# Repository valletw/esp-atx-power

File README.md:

# ESP32 ATX Power Controller

The purpose of this project is to control a computer remotely by connecting
directly to the ATX motherboard power IO control. The control will be done with
Home Assistant by using [ESPHome](https://esphome.io) firmware.

Custom software could be written by using ESP-IDF SDK but it is not the purpose
of this project.

## Hardware

Double 2.54mm pin headers are set for each ATX functionalities to manage:

- `PWR SW`: ATX power button
- `RST SW`: ATX reset button
- `PWR LED`: ATX power state LED
- `HDD LED`: ATX HDD activity LED

Two status LED are available:

- `PWR`: 3.3V state
- `STAT`: System status controlled by software

Two buttons are available for ESP32 boot sequence:

- `BOOT`: Control processor download mode on boot
- `EN`: Control processor reset

For advanced debug, the following connectors are available:

- 2x5 1.27mm pins header JTAG/SWD for external probe
- 4-pins Molex connector for UART

### Components choice

This project is based on an ESP32-C3 module to simplify design and ensure good
WiFi performance (with external antenna connector). ESP32 has been selected for
the big community to generate software and the frameworks available. Espressif
hardware design rules has been take into account following there
[documentation](https://docs.espressif.com/projects/esp-hardware-design-guidelines/en/latest/esp32c3/pcb-layout-design.html)

For easy debug and flashing, ESP32 with USB-CDC and JTAG support has been selected.
It allows to remove the USB-UART bridge of the previous design.

The optocouplers for electric isolation have been selected following the
[PiKVM](https://github.com/pikvm/pikvm) project experience. In the
[DIY PiKVM V2 instructions](https://docs.pikvm.org/v2/), the OMRON reference is
recommended. Others relays/optocouplers may not be sensitive enough or low-level
controlled.

The 3.3V to power all the components is generated from an LDO using the 5V of the
USB socket. It can also be powered from external 5V on pins header. Both external
5V and USB can be connected at the same time, a power MUX is used to switch between
both sources.

All others components has been selected from [JLCPCB](https://jlcpcb.com/parts/)
catalogue to minimize the cost and the assembly fees.

### Manufacturing

The board is manufactured by [JLCPCB](https://jlcpcb.com), here is the details
you will require to generate an order.

*Note: JLCPCB requests some modifications on output files, do not use direct
export from KiCad (check the FAQ)*

#### PCB

Files: [Gerbers](jlcpcb/gerbers.zip)

Configuration              | Value
---------------------------|---------------------------------
Base Materiel              | FR-4
Layers                     | 4
Dimensions                 | 76.56 x 25.10
Different design           | 1
Delivery format            | Single PCB
PCB thickness              | 1.6
PCB color                  | Green (other colors have fees)
Silkscreen                 | White
Materiel type              | FR4-Standard TG 135-140
Surface finish             | HASL
Specify layer sequence     | F_Cu / In1_Cu / In2_Cu / B_Cu
Impedance control          | Yes
Layer stackup              | JLC04161H-7628
Via covering               | Tented
Min via hole size/diameter | 0.3mm/0.45mm
Remove order number        | Specify a location

*Note: All options have not been detail here, keep default value.*

#### Assembly

Files: [BOM](jlcpcb/bom.csv), [CPL](jlcpcb/cpl.csv)

Configuration       | Value
--------------------|--------------------
PCBA type           | Economic
Assembly side       | Top
Tooling holes       | Added by JLCPCB

Verify "pick & place" orientations and positions on the web viewer

JLCPCB will add 2 tooling holes for assembly (1 mm diameter near the board corners).

*Note: All options have not been detail here, keep default value.*

### ESP32 Pinout

For those who want to reuse this project, here is the ESP32 pinout to manage the
different input/output.

Name              | Pin  | Direction
------------------|------|----------
System Status LED | IO8  | Output (strapping pin)
ATX Power Button  | IO0  | Output
ATX Reset Button  | IO1  | Output
ATX Power State   | IO3  | Input
ATX HDD Activity  | IO10 | Input

## ESPHome configuration

Device must be setup via USB connection the first time to flash the customized
firmware with sensors/buttons configuration.

Once it has been configured successfully, you should fix the device IP on your
router for easier Home Assistant configuration.

Note: Installation can be bypassed if already done or you can use docker image.
Check [ESPHome documentation](https://esphome.io/guides/getting_started_command_line.html)
for more details.

### Installation

```shell
pip install esphome
# Ensure your user session has the correct permission for serial port.
sudo usermod -a -G dialout <USERNAME>
```

### Customize

Depending of your installation and network, a `secrets.yaml` file must be
create with your specific configuration.

```yaml
# secrets.yaml
hostname: MyControllerHostname
wifi_ssid: MySSID
wifi_password: MyStrongPassphrase
wifi_fb_ssid: ATX Controller Fallback Hotspot
wifi_fb_password: StrongPassphrase
ota_password: MyOTAPassphrase
api_key: 32BytesBase64String
```

### Compile and flash

```shell
# Generate the firmware.
esphome compile esphome.yaml
# Flash the firmware to the ESP.
esphome run esphome.yaml
# Get logs.
esphome logs esphome.yaml
```

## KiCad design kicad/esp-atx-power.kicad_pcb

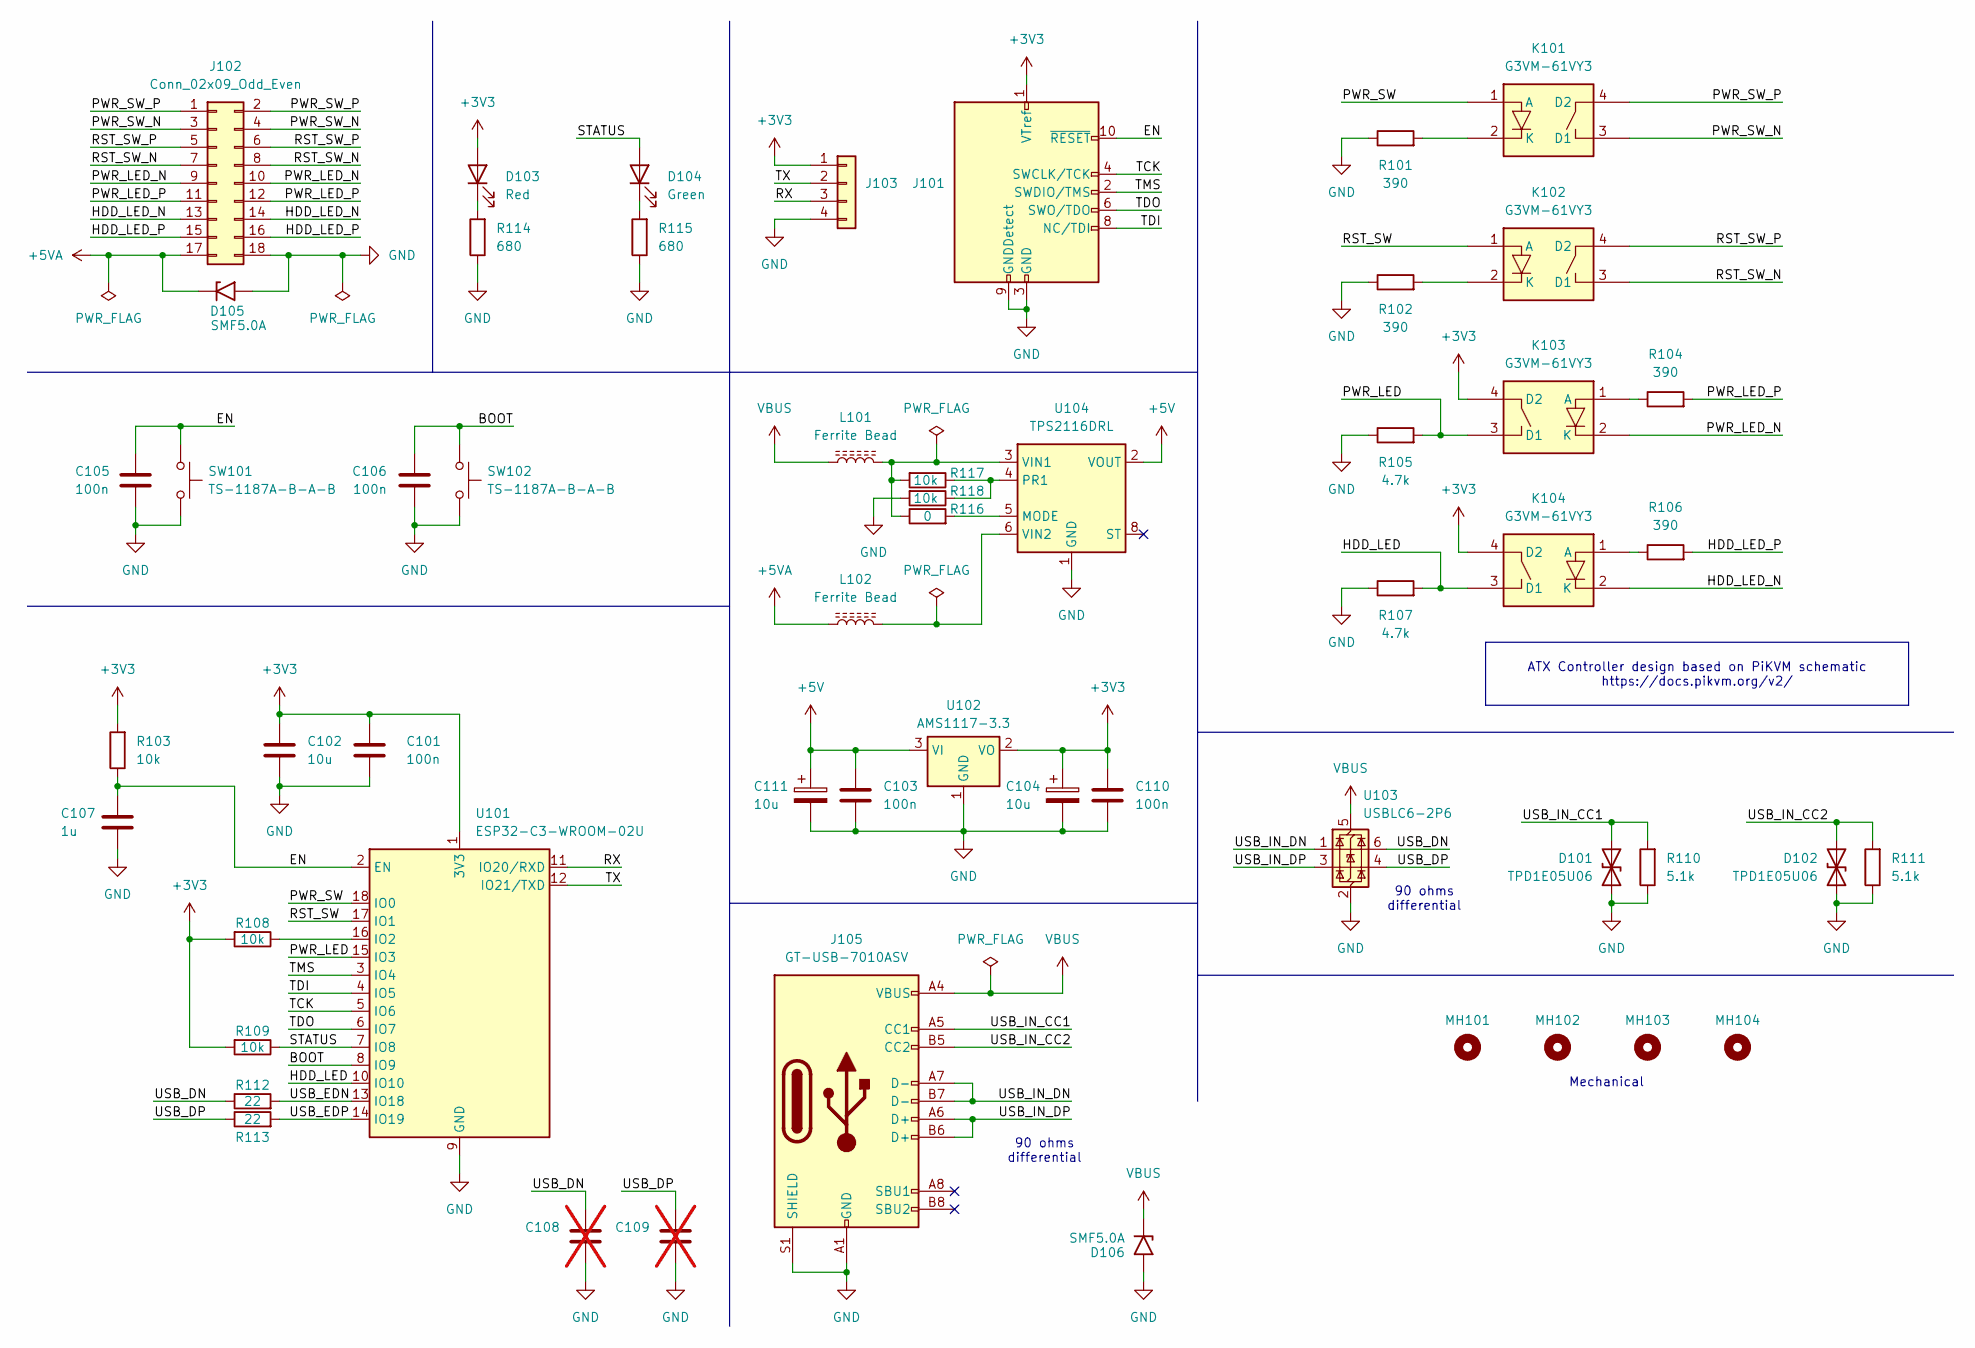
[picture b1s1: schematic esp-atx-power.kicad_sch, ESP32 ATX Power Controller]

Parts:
C101, C105, C106: 100n; C_0402_1005Metric; MFR Part # CL05B104KO5NNNC; LCSC Part # C1525
C102: 10u; C_0402_1005Metric; MFR Part # CL05A106MQ5NUNC; LCSC Part # C15525
C103, C110: 100n; C_0603_1608Metric; MFR Part # CC0603KRX7R9BB104; LCSC Part # C14663
C104, C111: 10u; CP_EIA-3216-18_Kemet-A; MFR Part # TAJA106K016RNJ; LCSC Part # C7171
C107: 1u; C_0402_1005Metric; MFR Part # CL05A105KA5NQNC; LCSC Part # C52923
C108, C109: C_0402_1005Metric; not fitted
D101, D102: TPD1E05U06; Texas_DPY0002A_0.6x1mm_P0.65mm; MFR Part # TPD1E05U06DPYR; LCSC Part # C436349
D103: Red; LED_0805_2012Metric; MFR Part # NCD0805R1; LCSC Part # C84256
D104: Green; LED_0805_2012Metric; MFR Part # KT-0805G; LCSC Part # C2297
D105, D106: SMF5.0A; D_SOD-123F; MFR Part # SMF5.0A; LCSC Part # C19077497
J101: Conn_ARM_JTAG_SWD_10; PinHeader_2x05_P1.27mm_Vertical_SMD; MFR Part # HX PZ1.27-2x5P TP; LCSC Part # C41376037
J102: Conn_02x09_Odd_Even; PinHeader_2x09_P2.54mm_Horizontal; MFR Part # PZ254-2-09-W-8.5; LCSC Part # C2894989
J103: Conn_01x04; Molex_PicoBlade_53261-0471_1x04-1MP_P1.25mm_Horizontal; MFR Part # 1.25T-4PSurface Mount，Right Angle; LCSC Part # C31597
J105: GT-USB-7010ASV; USB_C_Receptacle_G-Switch_GT-USB-7010ASV; MFR Part # GT-USB-7010ASV; LCSC Part # C2988369
K101, K102, K103, K104: G3VM-61VY3; SOP-4_3.8x4.1mm_P2.54mm; MFR Part # G3VM-61VY3(TR); LCSC Part # C2152318
L101, L102: Ferrite Bead; L_0603_1608Metric; MFR Part # BLM18PG121SN1D; LCSC Part # C14709
MH101, MH102, MH103, MH104: MountingHole_2.7mm_M2.5_ISO7380
R101, R102, R104, R106: 390; R_0603_1608Metric; MFR Part # 0603WAF3900T5E; LCSC Part # C23151
R103, R108, R109, R117, R118: 10k; R_0402_1005Metric; MFR Part # 0402WGF1002TCE; LCSC Part # C25744
R105, R107: 4.7k; R_0402_1005Metric; MFR Part # 0402WGF4701TCE; LCSC Part # C25900
R110, R111: 5.1k; R_0402_1005Metric; MFR Part # 0402WGF5101TCE; LCSC Part # C25905
R112, R113: 22; R_0402_1005Metric; MFR Part # 0402WGF220JTCE; LCSC Part # C25092
R114, R115: 680; R_0402_1005Metric; MFR Part # 0402WGF6800TCE; LCSC Part # C25130
R116: 0; R_0402_1005Metric; MFR Part # 0402WGF0000TCE; LCSC Part # C17168
SW101, SW102: TS-1187A-B-A-B; SW_Push_1P1T_XKB_TS-1187A; MFR Part # TS-1187A-B-A-B; LCSC Part # C318884
U101: ESP32-C3-WROOM-02U; MFR Part # ESP32-C3-WROOM-02U-N4; LCSC Part # C2926676
U102: AMS1117-3.3; SOT-223-3_TabPin2; MFR Part # AMS1117-3.3; LCSC Part # C6186
U103: USBLC6-2P6; SOT-666; MFR Part # USBLC6-2P6; LCSC Part # C15999
U104: TPS2116DRL; SOT-583-8; MFR Part # TPS2116DRLR; LCSC Part # C3235557

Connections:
+3V3: C101.2, C102.1, C104.1, C110.1, D103.2 (A), J101.1 (VTref), J103.1, K103.4 (D2), K104.4 (D2), R103.2, R108.2, R109.2, U101.1 (3V3), U102.2 (VO)
+5V: C103.1, C111.1, U102.3 (VI), U104.2 (VOUT), U104.7 (VOUT)
+5VA: D105.1 (A1), J102.17, L102.1
/BOOT: C106.1, SW102.1, U101.8 (IO9)
/EN: C105.1, C107.1, J101.10 (~RESET), R103.1, SW101.1, U101.2 (EN)
/HDD_LED: K104.3 (D1), R107.2, U101.10 (IO10)
/HDD_LED_N: J102.13, J102.14, K104.2 (K)
/HDD_LED_P: J102.15, J102.16, R106.2
/PWR_LED: K103.3 (D1), R105.2, U101.15 (IO3)
/PWR_LED_N: J102.9, J102.10, K103.2 (K)
/PWR_LED_P: J102.11, J102.12, R104.2
/PWR_SW: K101.1 (A), U101.18 (IO0)
/PWR_SW_N: J102.3, J102.4, K101.3 (D1)
/PWR_SW_P: J102.1, J102.2, K101.4 (D2)
/RST_SW: K102.1 (A), U101.17 (IO1)
/RST_SW_N: J102.7, J102.8, K102.3 (D1)
/RST_SW_P: J102.5, J102.6, K102.4 (D2)
/RX: J103.3, U101.11 (IO20/RXD)
/STATUS: D104.2 (A), R109.1, U101.7 (IO8)
/TCK: J101.4 (SWCLK/TCK), U101.5 (IO6)
/TDI: J101.8 (NC/TDI), U101.4 (IO5)
/TDO: J101.6 (SWO/TDO), U101.6 (IO7)
/TMS: J101.2 (SWDIO/TMS), U101.3 (IO4)
/TX: J103.2, U101.12 (IO21/TXD)
/USB_DN: C108.1, R112.1, U103.6 (I/O1)
/USB_DP: C109.1, R113.1, U103.4 (I/O2)
/USB_EDN: R112.2, U101.13 (IO18)
/USB_EDP: R113.2, U101.14 (IO19)
/USB_IN_CC1: D101.2 (A2), J105.A5 (CC1), R110.2
/USB_IN_CC2: D102.2 (A2), J105.B5 (CC2), R111.2
/USB_IN_DN: J105.A7 (D-), J105.B7 (D-), U103.1 (I/O1)
/USB_IN_DP: J105.A6 (D+), J105.B6 (D+), U103.3 (I/O2)
GND: C101.1, C102.2, C103.2, C104.2, C105.2, C106.2, C107.2, C108.2, C109.2, C110.2, C111.2, D101.1 (A1), D102.1 (A1), D105.2 (A2), D106.2 (A2), J101.3 (GND), J101.5 (GND), J101.9 (GNDDetect), J102.18, J103.4, J105.A1 (GND), J105.A12 (GND), J105.B1 (GND), J105.B12 (GND), J105.S1 (SHIELD), R101.1, R102.1, R105.1, R107.1, R110.1, R111.1, R114.1, R115.1, R118.2, SW101.2, SW102.2, U101.9 (GND), U101.19 (GND), U102.1 (GND), U103.2 (GND), U104.1 (GND)
unnamed: D103.1 (K), R114.2
unnamed: D104.1 (K), R115.2
unnamed: K101.2 (K), R101.2
unnamed: K102.2 (K), R102.2
unnamed: K103.1 (A), R104.1
unnamed: K104.1 (A), R106.1
unnamed: R108.1, U101.16 (IO2)
unnamed: R116.2, U104.5 (MODE)
unnamed: R117.1, R118.1, U104.4 (PR1)
unnamed: L101.2, R116.1, R117.2, U104.3 (VIN1)
unnamed: L102.2, U104.6 (VIN2)
VBUS: D106.1 (A1), J105.A4 (VBUS), J105.A9 (VBUS), J105.B4 (VBUS), J105.B9 (VBUS), L101.1, U103.5 (VBUS)

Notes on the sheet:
90 ohms differential
Mechanical
ATX Controller design based on PiKVM schematic https://docs.pikvm.org/v2/

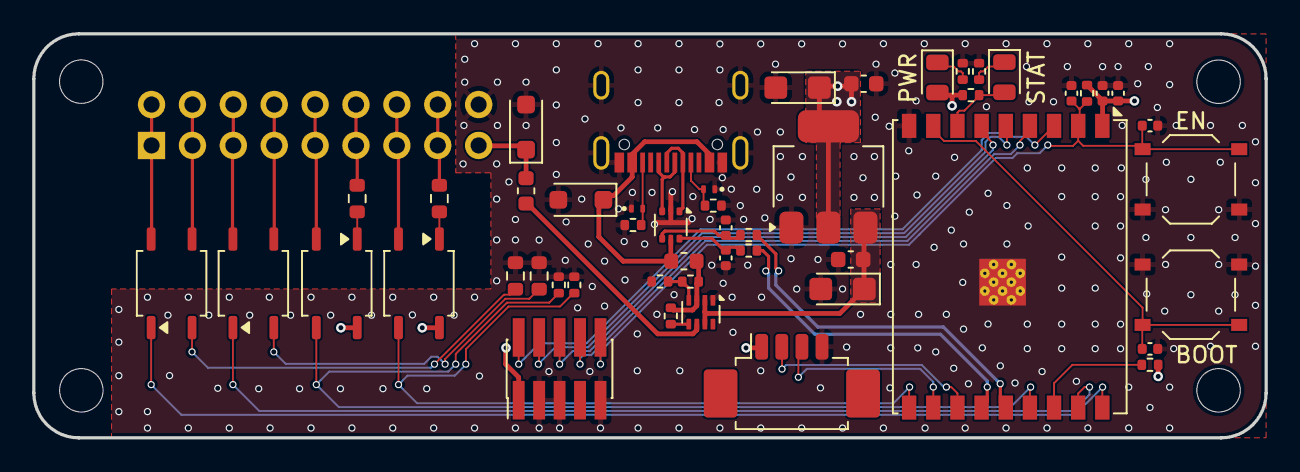
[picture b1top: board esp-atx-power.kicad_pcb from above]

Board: 4 copper layers, 76.6 x 25.1 mm, 55 parts (0 on the bottom side), 45 nets.

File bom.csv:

"Reference","Value","Qty","Footprint","LCSC Part #","MFR Part #","Manufacturer","Datasheet"
"C108,C109","~","2","Capacitor_SMD:C_0402_1005Metric","","","",""
"MH101,MH102,MH103,MH104","~","4","MountingHole:MountingHole_2.7mm_M2.5_ISO7380","","","","~"
"C101,C105,C106","100n","3","Capacitor_SMD:C_0402_1005Metric","C1525","CL05B104KO5NNNC","Samsung Electro-Mechanics","https://datasheet.lcsc.com/lcsc/2304140030_Samsung-Electro-M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"
"D104","Green","1","LED_SMD:LED_0805_2012Metric","C2297","KT-0805G","Hubei KENTO Elec","https://jlcpcb.com/api/file/downloadByFileSystemAccessId/863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"
"U102","AMS1117-3.3","1","Package_TO_SOT_SMD:SOT-223-3_TabPin2","C6186","AMS1117-3.3","Advanced Monolithic Systems","http://www.advanced-monolithic.com/pdf/ds1117.pdf"
"C104,C111","10u","2","Capacitor_Tantalum_SMD:CP_EIA-3216-18_Kemet-A","C7171","TAJA106K016RNJ","",""
"C103,C110","100n","2","Capacitor_SMD:C_0603_1608Metric","C14663","CC0603KRX7R9BB104","YAGEO","https://jlcpcb.com/api/file/downloadByFileSystemAccessId/857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"
"L101,L102","Ferrite Bead","2","Inductor_SMD:L_0603_1608Metric","C14709","BLM18PG121SN1D","Murata Electronics","https://jlcpcb.com/api/file/downloadByFileSystemAccessId/858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"
"C102","10u","1","Capacitor_SMD:C_0402_1005Metric","C15525","CL05A106MQ5NUNC","Samsung Electro-Mechanics","https://datasheet.lcsc.com/lcsc/2208231630_Samsung-Electro-M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"
"U103","USBLC6-2P6","1","Package_TO_SOT_SMD:SOT-666","C15999","USBLC6-2P6","STMicroeletronics","https://www.st.com/resource/en/datasheet/usblc6-2.pdf"
"R116","0","1","Resistor_SMD:R_0402_1005Metric","C17168","0402WGF0000TCE","UNI-ROYAL(Uniroyal Elec)","https://jlcpcb.com/api/file/downloadByFileSystemAccessId/857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"
"R101,R102,R104,R106","390","4","Resistor_SMD:R_0603_1608Metric","C23151","0603WAF3900T5E","UNI-ROYAL(Uniroyal Elec)","https://datasheet.lcsc.com/lcsc/2206010116_UNI-ROYAL-Uniroya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"
"R112,R113","22","2","Resistor_SMD:R_0402_1005Metric","C25092","0402WGF220JTCE","UNI-ROYAL(Uniroyal Elec)","https://jlcpcb.com/api/file/downloadByFileSystemAccessId/857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"
"R114,R115","680","2","Resistor_SMD:R_0402_1005Metric","C25130","0402WGF6800TCE","UNI-ROYAL(Uniroyal Elec)","https://jlcpcb.com/api/file/downloadByFileSystemAccessId/857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"
"R103,R108,R109,R117,R118","10k","5","Resistor_SMD:R_0402_1005Metric","C25744","0402WGF1002TCE","UNI-ROYAL(Uniroyal Elec)","https://datasheet.lcsc.com/lcsc/2206010100_UNI-ROYAL-Uniroya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"
"R105,R107","4.7k","2","Resistor_SMD:R_0402_1005Metric","C25900","0402WGF4701TCE","UNI-ROYAL(Uniroyal Elec)","https://datasheet.lcsc.com/lcsc/2206010045_UNI-ROYAL-Uniroya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"
"R110,R111","5.1k","2","Resistor_SMD:R_0402_1005Metric","C25905","0402WGF5101TCE","UNI-ROYAL(Uniroyal Elec)","https://datasheet.lcsc.com/lcsc/2206010045_UNI-ROYAL-Uniroya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"
"J103","Conn_01x04","1","Connector_Molex:Molex_PicoBlade_53261-0471_1x04-1MP_P1.25mm_Horizontal","C31597","1.25T-4PSurface Mount，Right Angle","BOOMELE(Boom Precision Elec)","https://jlcpcb.com/api/file/downloadByFileSystemAccessId/858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"
"C107","1u","1","Capacitor_SMD:C_0402_1005Metric","C52923","CL05A105KA5NQNC","Samsung Electro-Mechanics","https://datasheet.lcsc.com/lcsc/2304140030_Samsung-Electro-M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"
"D103","Red","1","LED_SMD:LED_0805_2012Metric","C84256","NCD0805R1","Foshan NationStar Optoelectronics","https://jlcpcb.com/api/file/downloadByFileSystemAccessId/855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"
"SW101,SW102","TS-1187A-B-A-B","2","Button_Switch_SMD:SW_Push_1P1T_XKB_TS-1187A","C318884","TS-1187A-B-A-B","XKB Connectivity","https://datasheet.lcsc.com/lcsc/2304140030_XKB-Connectivity-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"
"D101,D102","TPD1E05U06","2","Package_SON:Texas_DPY0002A_0.6x1mm_P0.65mm","C436349","TPD1E05U06DPYR","Texas Instruments","https://www.ti.com/lit/ds/symlink/tpd4e05u06.pdf"
"K101,K102,K103,K104","G3VM-61VY3","4","Package_SO:SOP-4_3.8x4.1mm_P2.54mm","C2152318","G3VM-61VY3(TR)","Omron Electronics","https://components.omron.com/sites/components.omron.com.eu/f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"
"J102","Conn_02x09_Odd_Even","1","Connector_PinHeader_2.54mm:PinHeader_2x09_P2.54mm_Horizontal","C2894989","PZ254-2-09-W-8.5","HCTL","https://jlcpcb.com/api/file/downloadByFileSystemAccessId/858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"
"U101","ESP32-C3-WROOM-02U","1","RF_Module:ESP32-C3-WROOM-02U","C2926676","ESP32-C3-WROOM-02U-N4","Espressif Systems","https://www.espressif.com/sites/default/files/documentation/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"
"J105","GT-USB-7010ASV","1","Connector_USB:USB_C_Receptacle_G-Switch_GT-USB-7010ASV","C2988369","GT-USB-7010ASV","G-Switch","https://datasheet.lcsc.com/lcsc/2303271630_G-Switch-GT-USB-7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"
"U104","TPS2116DRL","1","Package_TO_SOT_SMD:SOT-583-8","C3235557","TPS2116DRLR","Texas Instruments","https://www.ti.com/lit/ds/symlink/tps2116.pdf"
"D105,D106","SMF5.0A","2","Diode_SMD:D_SOD-123F","C19077497","SMF5.0A","hongjiacheng","https://jlcpcb.com/api/file/downloadByFileSystemAccessId/856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"
"J101","Conn_ARM_JTAG_SWD_10","1","Connector_PinHeader_1.27mm:PinHeader_2x05_P1.27mm_Vertical_SMD","C41376037","HX PZ1.27-2x5P TP","hanxia","http://infocenter.arm.com/help/topic/com.arm.doc.ddi0314h/DD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"

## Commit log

2024-01-21 Add KiCad project files and custom component libraroes
2024-02-05 Provide KiCad output files
    - Schematic
    - BOM
    - Gerber
    - Render
2024-02-05 Add unboxed image
2024-02-05 Provide ESPHome configuration file
2024-02-05 Add README
2024-02-05 Fix RTS/DTR and increase LEDs resistors
    - RTS/DTR has been inverted and RTS assertin doesn't reset the board.
    - Increase the LED resistors to decrease brightness
    - Change JLCPCB order number position
2025-08-29 Update WiFi TX power with fast connection
    Mitigate "auth expired" issue
2025-08-29 Add WiFi RSSI sensor
2025-09-11 Fix ESPHome OTA configuration
2025-09-11 Bump to release 1.0.2
2025-09-11 Generate new KiCad output files
2025-09-11 Update board form factor and change ESP module
    - PCB antenna is not well working inside computer casing
    - Select an ESP with external antenna connector
    - Remove USB-UART bridge which is no longer required for flashing
    - Use on unique pin header instead of 4
    - Add 5V external power supply in case USB port is not available
2025-10-07 Update ESPHome pinout configuration
2025-10-07 Update documentation
2025-10-07 Fix TVS diode orientation
    The selected diode was not bidirectional, update schematic symbol
    to take it into account and fix orientation on VBUS (short circuit).
2026-01-29 Update obsolete components
    - G3VM-61D1 is obselete and not manufactured anymore. A similar
    reference has been set with smaller package
    - Molex connector for debug is not available on JLCPCB anymore.
    Alternative found with similar footprint

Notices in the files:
kicad/esp-atx-power.kicad_pcb:
MIT License
